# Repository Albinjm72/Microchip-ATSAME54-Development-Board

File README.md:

<div align="center">

# ATSAME54N20A-AU Development Board

**A custom-designed development board built around the Microchip ATSAME54N20A-AU (ARM Cortex-M4F)**

Designed end-to-end in KiCad — schematic, routing, and silkscreen.

</div>

---

## Overview

This is a fully custom development board designed from a bare microcontroller datasheet up — power architecture, signal routing, and silkscreen branding all done by hand in KiCad, not adapted from a reference design.

## Features

| Feature | Detail |
|---|---|
| **MCU** | Microchip ATSAME54N20A-AU — ARM Cortex-M4F, 120MHz, 1MB flash, 100-pin TQFP |
| **USB** | USB Type-C connector (power + native USB) |
| **CAN** | Onboard CAN controller/transceiver for real bus communication |
| **Storage** | microSD card slot (SDHC) + external QSPI flash |
| **Debug** | SWD programming/debug header |
| **Indicators** | 1x power LED, 2x user-controllable LEDs |
| **I/O** | Dual 2-row GPIO headers (one on each side) — breadboard-compatible pitch |

## Board layout

- **Left and right edges:** two rows of breakout headers on each side, broken out to standard 2.54mm pitch for direct breadboard use
- **Top section:** power, USB-C, SD card slot, SWD header
- **Center:** ATSAME54N20A-AU (TQFP-100)

## Getting started

1. Clone this repository
2. Open `ATSAME54N20A-AU.kicad_pro` in **KiCad 10** or later
3. Manufacturing-ready files are already generated under `gerber_to_order/` if you just want to order the board as-is

## Programming

Program and debug via the onboard **SWD header** using any ARM-compatible probe (ST-Link, J-Link, Atmel-ICE, or similar), through OpenOCD/GDB or MPLAB X.

## Bill of Materials

Full BOM with reference designators, values, and footprints is in `production/bom.csv`.

## Revision history

See [CHANGELOG.md](CHANGELOG.md) for what changed between board revisions.

## License

Licensed under [CERN-OHL-S v2](LICENSE).

## Status

🔧 **Active development** — first hardware revision fabricated, pending assembly and bring-up testing.

---

<div align="center">
<sub>Built with KiCad · Designed by Albin Jose Mathew</sub>
</div>

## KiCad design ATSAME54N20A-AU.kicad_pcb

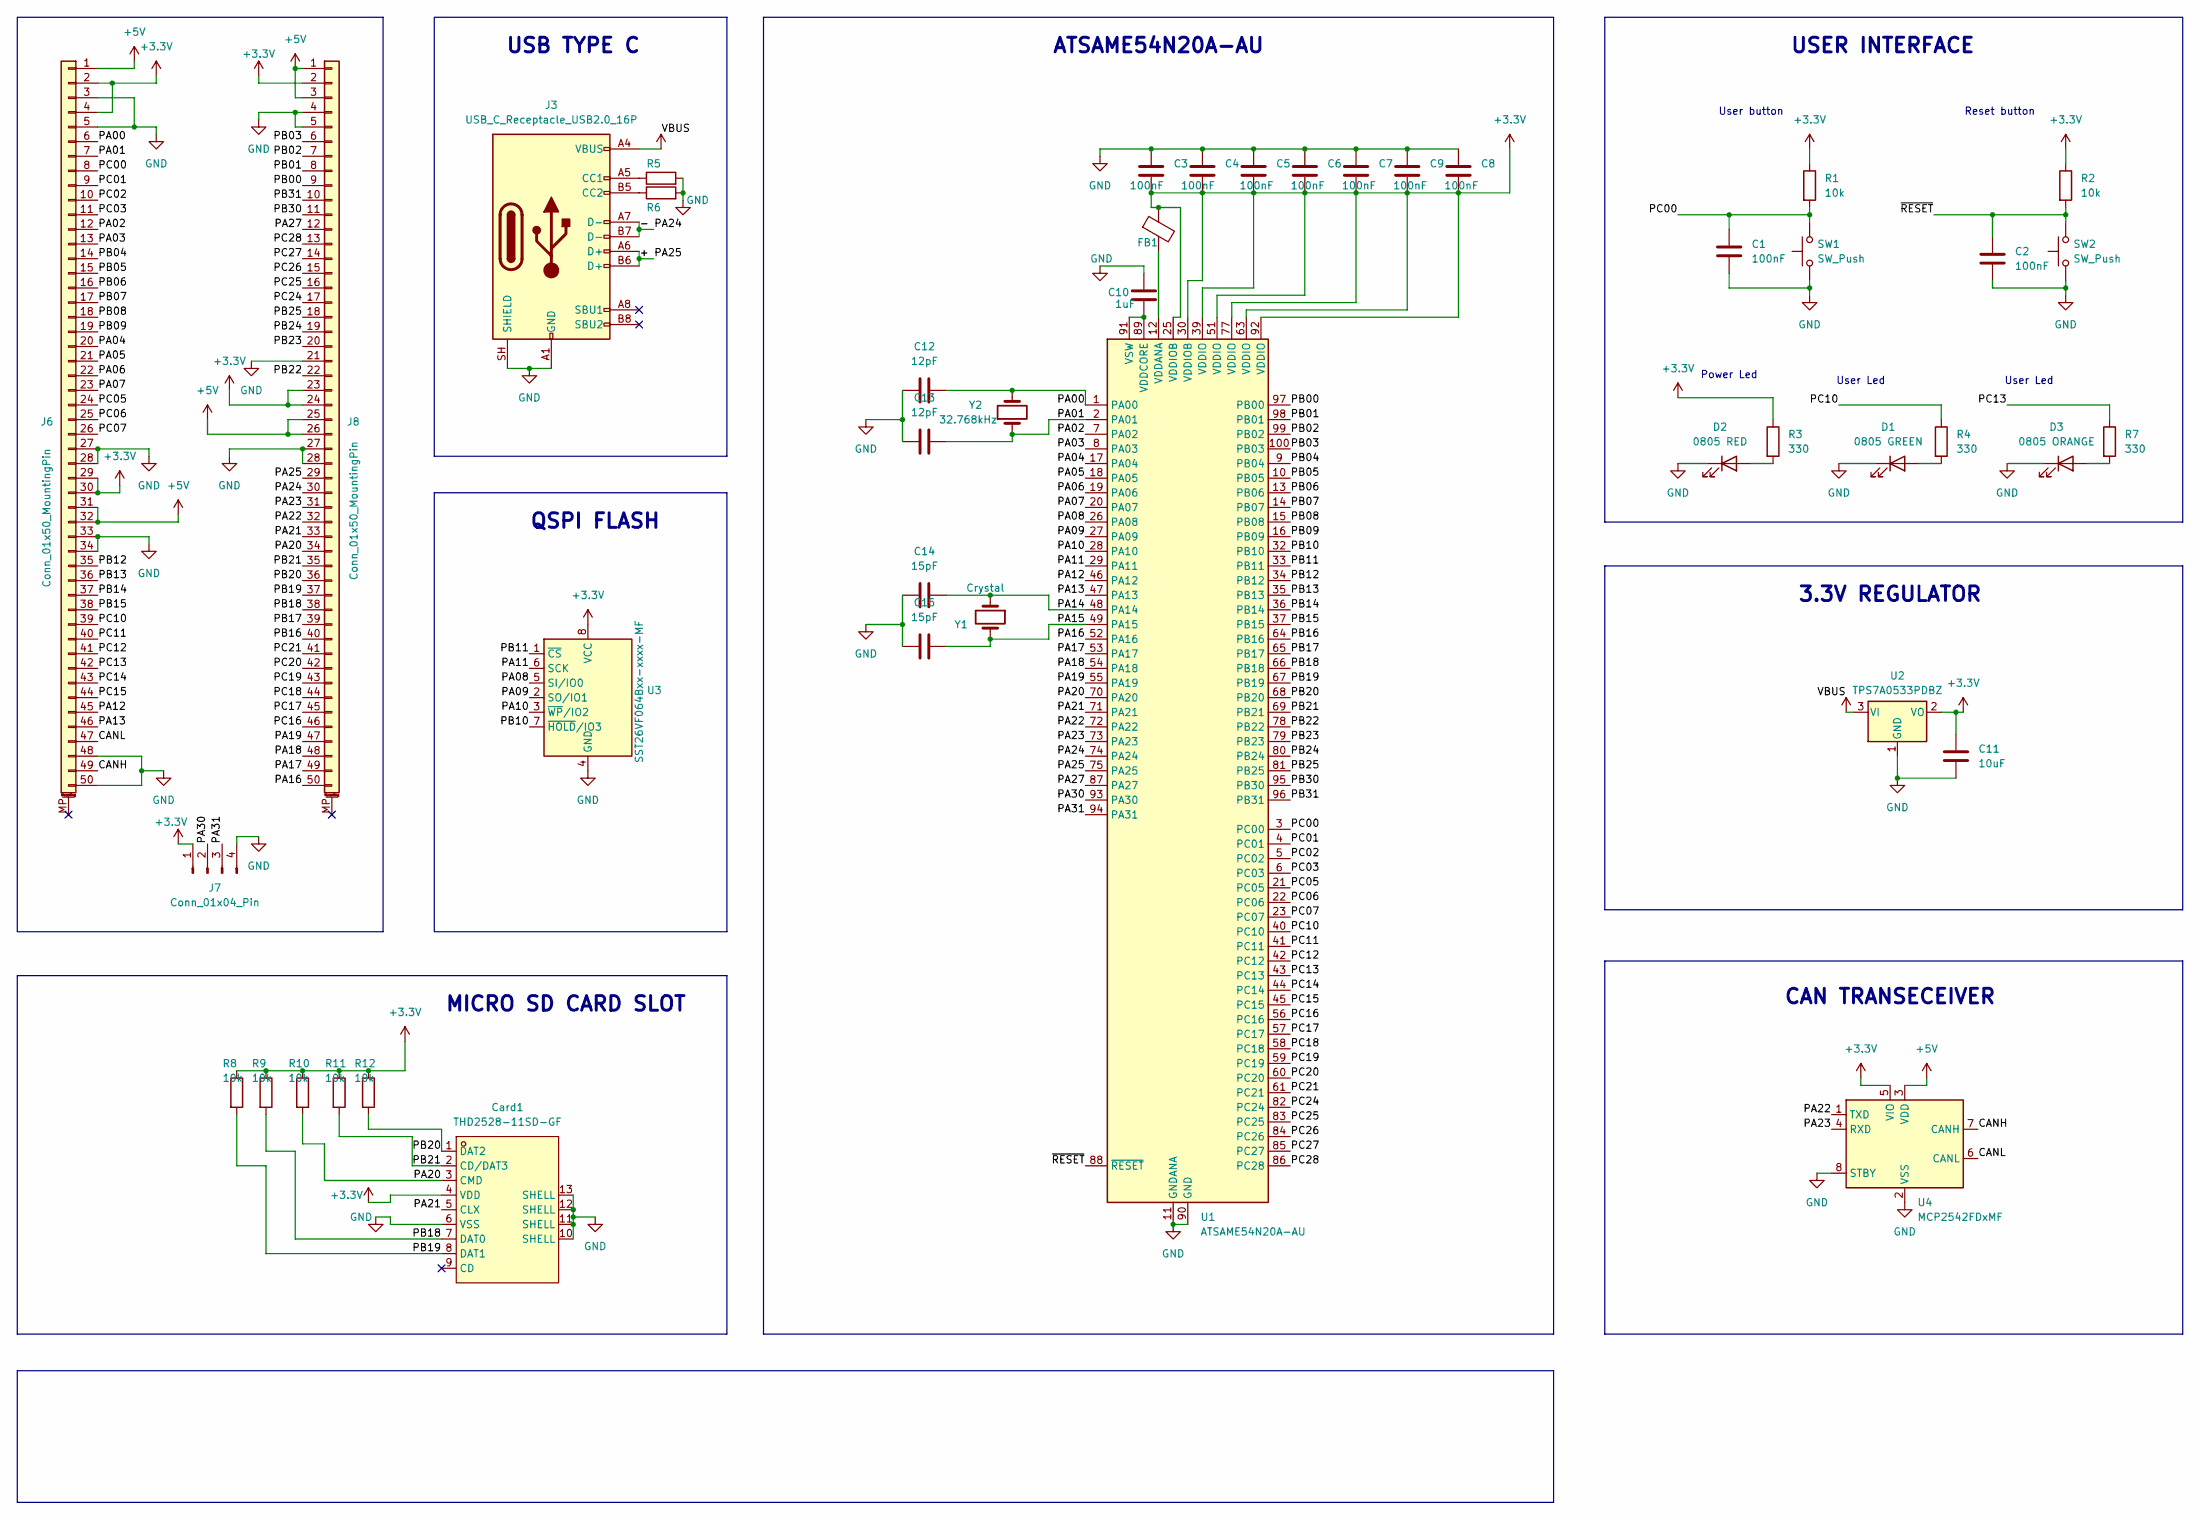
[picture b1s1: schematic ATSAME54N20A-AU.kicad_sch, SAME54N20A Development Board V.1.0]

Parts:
C1, C2, C3, C4, C5, C6, C7, C8, C9: 100nF; C_0402_1005Metric_Pad0.74x0.62mm_HandSolder
C10: 1uF; C_0603_1608Metric
C11: 10uF; C_0603_1608Metric
C12, C13: 12pF; C_0402_1005Metric_Pad0.74x0.62mm_HandSolder
C14, C15: 15pF; C_0402_1005Metric_Pad0.74x0.62mm_HandSolder
Card1: THD2528-11SD-GF; TF-SMD_THD2528-11SD-GF; MPN THD2528-11SD-GF; LCSC Part C283232
D1: 0805 GREEN; LED_0805_2012Metric
D2: 0805 RED; LED_0805_2012Metric
D3: 0805 ORANGE; LED_0805_2012Metric
FB1: 600ohm@100MHz; L_0402_1005Metric_Pad0.77x0.64mm_HandSolder
J3: USB_C_Receptacle_USB2.0_16P; USB_C_Receptacle_HCTL_HC-TYPE-C-16P-01A
J6, J8: Conn_01x50_MountingPin; PinSocket_2x25_P2.54mm_Vertical
J7: Conn_01x04_Pin; PinSocket_1x04_P2.54mm_Vertical
R1, R2, R5, R6, R8, R9, R10, R11, R12: 10k; R_0402_1005Metric_Pad0.72x0.64mm_HandSolder
R3, R4, R7: 330; R_0402_1005Metric_Pad0.72x0.64mm_HandSolder
SW1, SW2: SW_Push; SW_Push_1P1T_NO_Vertical_Wuerth_434133025816
U1: ATSAME54N20A-AU; TQFP-100_14x14mm_P0.5mm
U2: TPS7A0533PDBZ; SOT-223-3_TabPin2
U3: SST26VF064Bxx-xxxx-MF; SOIJ-8_L5.3-W5.3-P1.27-LS7.9-BL
U4: MCP2542FDxMF; SOIC-8-1EP_3.9x4.9mm_P1.27mm_EP2.41x3.3mm
Y1: Crystal; Crystal_SMD_2520-4Pin_2.5x2.0mm
Y2: 32.768kHz; Crystal_SMD_3215-2Pin_3.2x1.5mm

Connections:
+3.3V: C3.2, C4.2, C5.2, C6.2, C7.2, C8.2, C9.2, C11.1, Card1.4 (VDD), FB1.1, J6.2, J6.4, J6.29, J6.30, J7.1, J8.2, J8.23, J8.24, R1.1, R2.1, R3.1, R8.1, R9.1, R10.1, R11.1, R12.1, U1.25 (VDDIOB), U1.30 (VDDIOB), U1.39 (VDDIO), U1.51 (VDDIO), U1.63 (VDDIO), U1.77 (VDDIO), U1.92 (VDDIO), U2.2 (VO), U3.8 (VCC), U4.5 (VIO)
+5V: J3.A4 (VBUS), J3.A9 (VBUS), J3.B4 (VBUS), J3.B9 (VBUS), J6.1, J6.31, J6.32, J8.1, J8.3, J8.25, J8.26, U2.3 (VI), U4.3 (VDD)
/+: J3.A6 (D+), J3.B6 (D+), J8.29, U1.75 (PA25)
/-: J3.A7 (D-), J3.B7 (D-), J8.30, U1.74 (PA24)
/CANH: J6.49, U4.7 (CANH)
/CANL: J6.47, U4.6 (CANL)
/PA00: C12.2, J6.6, U1.1 (PA00), Y2.2
/PA01: C13.2, J6.7, U1.2 (PA01), Y2.1
/PA02: J6.12, U1.7 (PA02)
/PA03: J6.13, U1.8 (PA03)
/PA04: J6.20, U1.17 (PA04)
/PA05: J6.21, U1.18 (PA05)
/PA06: J6.22, U1.19 (PA06)
/PA07: J6.23, U1.20 (PA07)
/PA08: U1.26 (PA08), U3.5 (SI/IO0)
/PA09: U1.27 (PA09), U3.2 (SO/IO1)
/PA10: U1.28 (PA10), U3.3 (~WP/IO2)
/PA11: U1.29 (PA11), U3.6 (SCK)
/PA12: J6.45, U1.46 (PA12)
/PA13: J6.46, U1.47 (PA13)
/PA14: C14.2, U1.48 (PA14), Y1.1
/PA15: C15.2, U1.49 (PA15), Y1.2
/PA16: J8.50, U1.52 (PA16)
/PA17: J8.49, U1.53 (PA17)
/PA18: J8.48, U1.54 (PA18)
/PA19: J8.47, U1.55 (PA19)
/PA20: Card1.3 (CMD), J8.34, R10.2, U1.70 (PA20)
/PA21: Card1.5 (CLX), J8.33, U1.71 (PA21)
/PA22: J8.32, U1.72 (PA22), U4.1 (TXD)
/PA23: J8.31, U1.73 (PA23), U4.4 (RXD)
/PA27: J8.12, U1.87 (PA27)
/PA30: J7.2, U1.93 (PA30)
/PA31: J7.3, U1.94 (PA31)
/PB00: J8.9, U1.97 (PB00)
/PB01: J8.8, U1.98 (PB01)
/PB02: J8.7, U1.99 (PB02)
/PB03: J8.6, U1.100 (PB03)
/PB04: J6.14, U1.9 (PB04)
/PB05: J6.15, U1.10 (PB05)
/PB06: J6.16, U1.13 (PB06)
/PB07: J6.17, U1.14 (PB07)
/PB08: J6.18, U1.15 (PB08)
/PB09: J6.19, U1.16 (PB09)
/PB10: U1.32 (PB10), U3.7 (~HOLD/IO3)
/PB11: U1.33 (PB11), U3.1 (~CS)
/PB12: J6.35, U1.34 (PB12)
/PB13: J6.36, U1.35 (PB13)
/PB14: J6.37, U1.36 (PB14)
/PB15: J6.38, U1.37 (PB15)
/PB16: J8.40, U1.64 (PB16)
/PB17: J8.39, U1.65 (PB17)
/PB18: Card1.7 (DAT0), J8.38, R9.2, U1.66 (PB18)
/PB19: Card1.8 (DAT1), J8.37, R8.2, U1.67 (PB19)
/PB20: Card1.1 (DAT2), J8.36, R12.2, U1.68 (PB20)
/PB21: Card1.2 (CD/DAT3), J8.35, R11.2, U1.69 (PB21)
/PB22: J8.22, U1.78 (PB22)
/PB23: J8.20, U1.79 (PB23)
/PB24: J8.19, U1.80 (PB24)
/PB25: J8.18, U1.81 (PB25)
/PB30: J8.11, U1.95 (PB30)
/PB31: J8.10, U1.96 (PB31)
/PC00: C1.1, J6.8, R1.2, SW1.2, U1.3 (PC00)
/PC01: J6.9, U1.4 (PC01)
/PC02: J6.10, U1.5 (PC02)
/PC03: J6.11, U1.6 (PC03)
/PC05: J6.24, U1.21 (PC05)
/PC06: J6.25, U1.22 (PC06)
/PC07: J6.26, U1.23 (PC07)
/PC10: J6.39, R4.1, U1.40 (PC10)
/PC11: J6.40, U1.41 (PC11)
/PC12: J6.41, U1.42 (PC12)
/PC13: J6.42, R7.1, U1.43 (PC13)
/PC14: J6.43, U1.44 (PC14)
/PC15: J6.44, U1.45 (PC15)
/PC16: J8.46, U1.56 (PC16)
/PC17: J8.45, U1.57 (PC17)
/PC18: J8.44, U1.58 (PC18)
/PC19: J8.43, U1.59 (PC19)
/PC20: J8.42, U1.60 (PC20)
/PC21: J8.41, U1.61 (PC21)
/PC24: J8.17, U1.82 (PC24)
/PC25: J8.16, U1.83 (PC25)
/PC26: J8.15, U1.84 (PC26)
/PC27: J8.14, U1.85 (PC27)
/PC28: J8.13, U1.86 (PC28)
/~RESET: C2.1, R2.2, SW2.2, U1.88 (~RESET)
GND: C1.2, C2.2, C3.1, C4.1, C5.1, C6.1, C7.1, C8.1, C9.1, C10.1, C11.2, C12.1, C13.1, C14.1, C15.1, Card1.6 (VSS), Card1.10 (SHELL), Card1.11 (SHELL), Card1.12 (SHELL), Card1.13 (SHELL), D1.1 (K), D2.1 (K), D3.1 (K), J3.A1 (GND), J3.A12 (GND), J3.B1 (GND), J3.B12 (GND), J3.SH (SHIELD), J6.3, J6.5, J6.27, J6.28, J6.33, J6.34, J6.48, J6.50, J7.4, J8.4, J8.5, J8.21, J8.27, J8.28, R5.2, R6.2, SW1.1, SW2.1, U1.11 (GNDANA), U1.24 (GND), U1.31 (GND), U1.38 (GND), U1.50 (GND), U1.62 (GND), U1.76 (GND), U1.90 (GND), U2.1 (GND), U3.4 (GND), U4.2 (VSS), U4.8 (STBY), U4.9 (VSS)
unnamed: D1.2 (A), R4.2
unnamed: D2.2 (A), R3.2
unnamed: D3.2 (A), R7.2
unnamed: J3.A5 (CC1), R5.1
unnamed: J3.B5 (CC2), R6.1
unnamed: FB1.2, U1.12 (VDDANA)
unnamed: C10.2, U1.89 (VDDCORE), U1.91 (VSW)

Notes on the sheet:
User Led
USER INTERFACE
USB TYPE C
Power Led
User button
QSPI FLASH
3.3V REGULATOR
MICRO SD CARD SLOT
ATSAME54N20A-AU
CAN TRANSECEIVER
Reset button

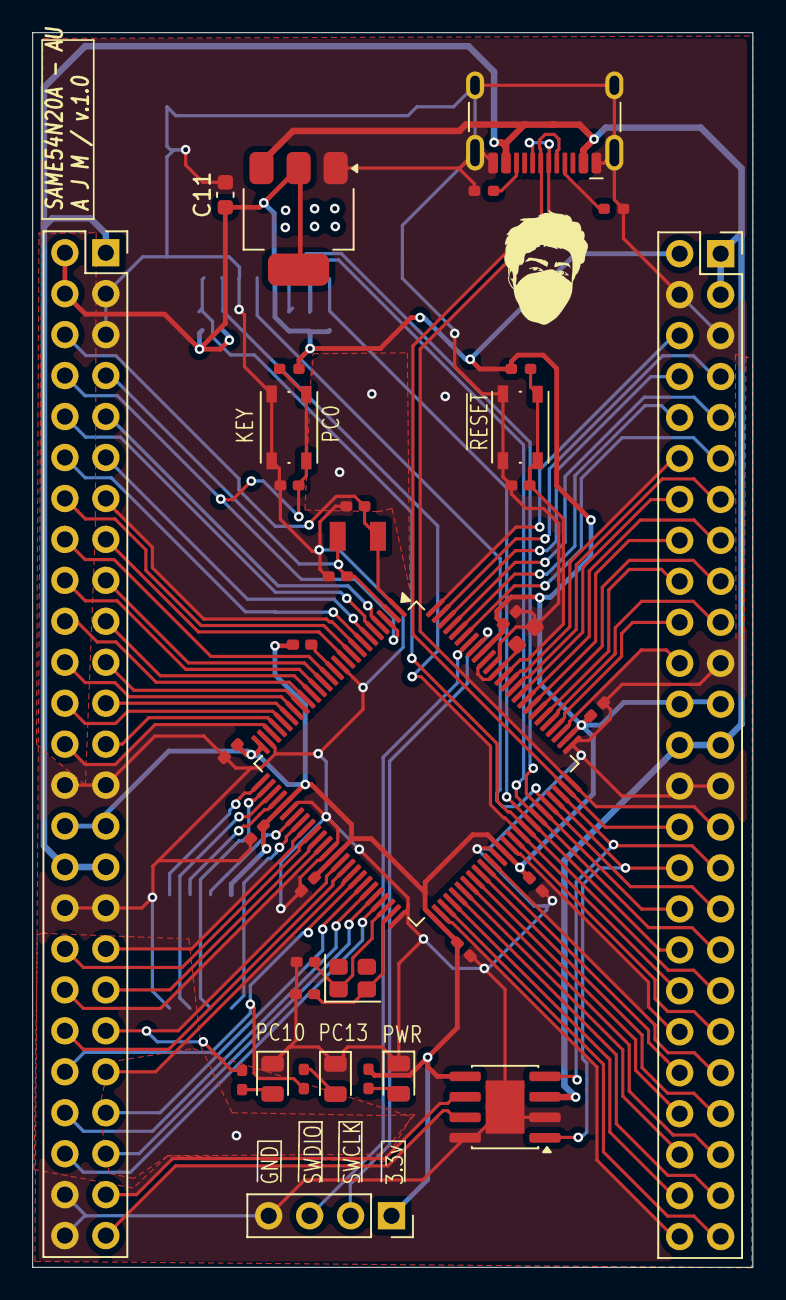
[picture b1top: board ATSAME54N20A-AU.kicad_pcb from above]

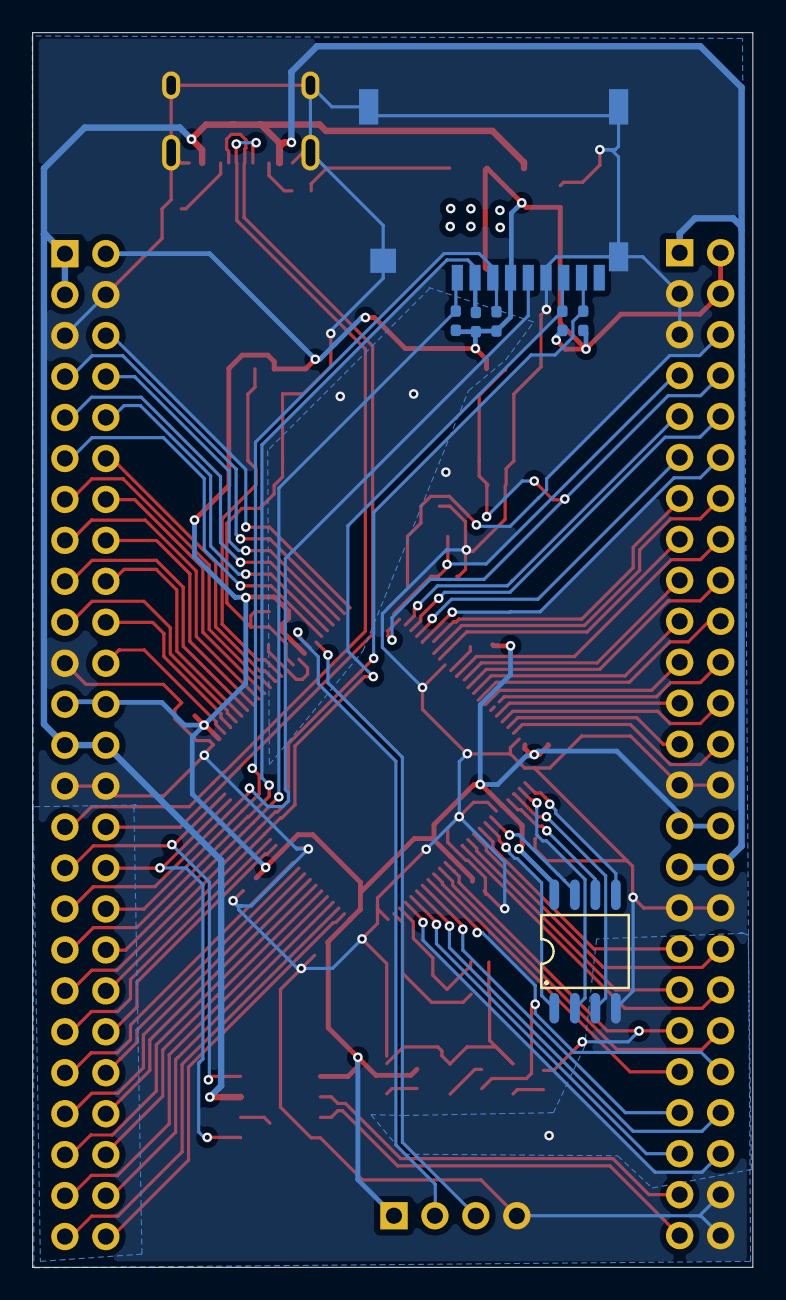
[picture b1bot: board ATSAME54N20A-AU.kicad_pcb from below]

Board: 2 copper layers, 44.7 x 76.6 mm, 44 parts (7 on the bottom side), 94 nets.

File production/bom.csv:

Designator,Footprint,Quantity,Value,LCSC Part #
"C1, C2, C3, C4, C5, C6, C7, C8, C9",0402,9,100nF,
C10,0603,1,1uF,
C11,0603,1,10uF,
"C12, C13",0402,2,12pF,
"C14, C15",0402,2,15pF,
CARD1,TF-SMD_THD2528-11SD-GF,1,THD2528-11SD-GF,C283232
D1,0805,1,0805 GREEN,
D2,0805,1,0805 RED,
D3,0805,1,0805 ORANGE,
FB1,0402,1,600ohm@100MHz,
J3,USB_C_Receptacle_HCTL_HC-TYPE-C-16P-01A,1,USB_C_Receptacle_USB2.0_16P,
"J6, J8",PinSocket_2x25_P2.54mm_Vertical,2,Conn_01x50_MountingPin,
J7,PinSocket_1x04_P2.54mm_Vertical,1,Conn_01x04_Pin,
"R1, R10, R11, R12, R2, R5, R6, R8, R9",0402,9,10k,
"R3, R4, R7",0402,3,330,
"SW1, SW2",SW_Push_1P1T_NO_Vertical_Wuerth_434133025816,2,SW_Push,
U1,TQFP-100_14x14mm_P0.5mm,1,ATSAME54N20A-AU,
U2,SOT-223-3_TabPin2,1,TPS7A0533PDBZ,
U3,SOIJ-8_L5.3-W5.3-P1.27-LS7.9-BL,1,SST26VF064Bxx-xxxx-MF,C638561
U4,SOIC-8-1EP_3.9x4.9mm_P1.27mm_EP2.41x3.3mm,1,MCP2542FDxMF,
Y1,Crystal_SMD_2520-4Pin_2.5x2.0mm,1,Crystal,
Y2,Crystal_SMD_3215-2Pin_3.2x1.5mm,1,32.768kHz,
